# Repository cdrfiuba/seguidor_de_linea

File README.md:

# Robot Seguidor de Línea

Test de seguidor de línea para competiciones.
Nombre pendiente.

## Estructura del proyecto
Boceto de la estructura del proyecto

```bash
.
├── placa_sensor
│   ├── kicad_sch
│   └── kicad_pcb
├── placa_seguidor
│   ├── kicad_sch
│   └── kicad_pcb
├── modelo
│   └── seguidor.FCStd
├── include
│   ├── file1.h
│   └── file2.h
├── src
│   ├── file1.ino
│   └── file2.ino
├── res
│   ├── datasheets.pdf
│   ├── images.png
│   └── referencias o links
└── README.md
```

## Requisitos
 - 20cm largo x 14cm de ancho x 10cm de alto
 - Area mínima de 23mm x 14mm. Visible. No pueden ser secciones de la batería.
 - No control remoto, o que solo de la orden de salida
 - Indicador luminoso (fijo o intermitente) que muestra cuando el robot inicia a correr.
 - Ruedas sin adherentes

## TODOs
 - ~~Rediseñar la placa de sensores (corregir errores) y mandar al lci~~
 - ~~Puente H~~
 - ~~Arduino Nano o ATmega328~~ y programarlo
 - ~~Comprar Placa Experimental~~
 - ~~Elegir batería ~~
 - Hacer un diagrama tal vez de como seguir el proyecto
 - ~~Hacér una bitácora~~ (subirla al repo?)
 - Agregar pagina de documentación (KiBot)
 - ~~Agregar una lista de compras que puedan editar todos~~
 - ~~Terminar de Soldar/limpiar modulo de sensores chequeando continuidad (Ciin lo hace el jueves)~~
 - ~~Probar modulo se sensores con arduino (Armar código de prueba) ~~
 - Comprar Resistencias, capacitores (1206), diodos schottsky, hembra y macho (90 grados)
 - Soldar puente h anterior para probar
 - Medir las ruedas/bandas de caucho que se usará en la compe
 - Ajustar el modelo 3D del interior de la rueda
 - Soldar placa

## Artículos pendientes
 - 4 Capacitores 100nf (Puente H)
 - 8 x Diodos Schottsky 1N4007  (Puente H)
 - 1R de 1K y 1 de 330 SMD (1206)
 - 1 (+1) 74HC14 Schmitt Trigger THT
 - 2 DIP14

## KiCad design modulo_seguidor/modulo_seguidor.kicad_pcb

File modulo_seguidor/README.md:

# Modulo Seguidor

Este módulo ejecuta las funciones propias de un seguidor de línea, procesar las lecturas del módulo sensor, e integra el puente H L298N para dirigir los motores.

Vista previa de la placa desde arriba

## Diagrama

## TODOs
 - ~~Revisar las medidas de la placa (tomar en cuenta los bordes de la placa que no tienen agujeros)~~
 - Revisar los footprints de las resistencias y de los capacitores
 - Hacer espacio para la ruedita omnidireccional
 - ~~Acomodar los componentes y hacer las conexiones~~
 - Exportar a un modelo 3D (opcional)
 - ~~Probar en placa separada el modulo puente H~~
 - ~~Reemplazar conexiones de cables por housings~~

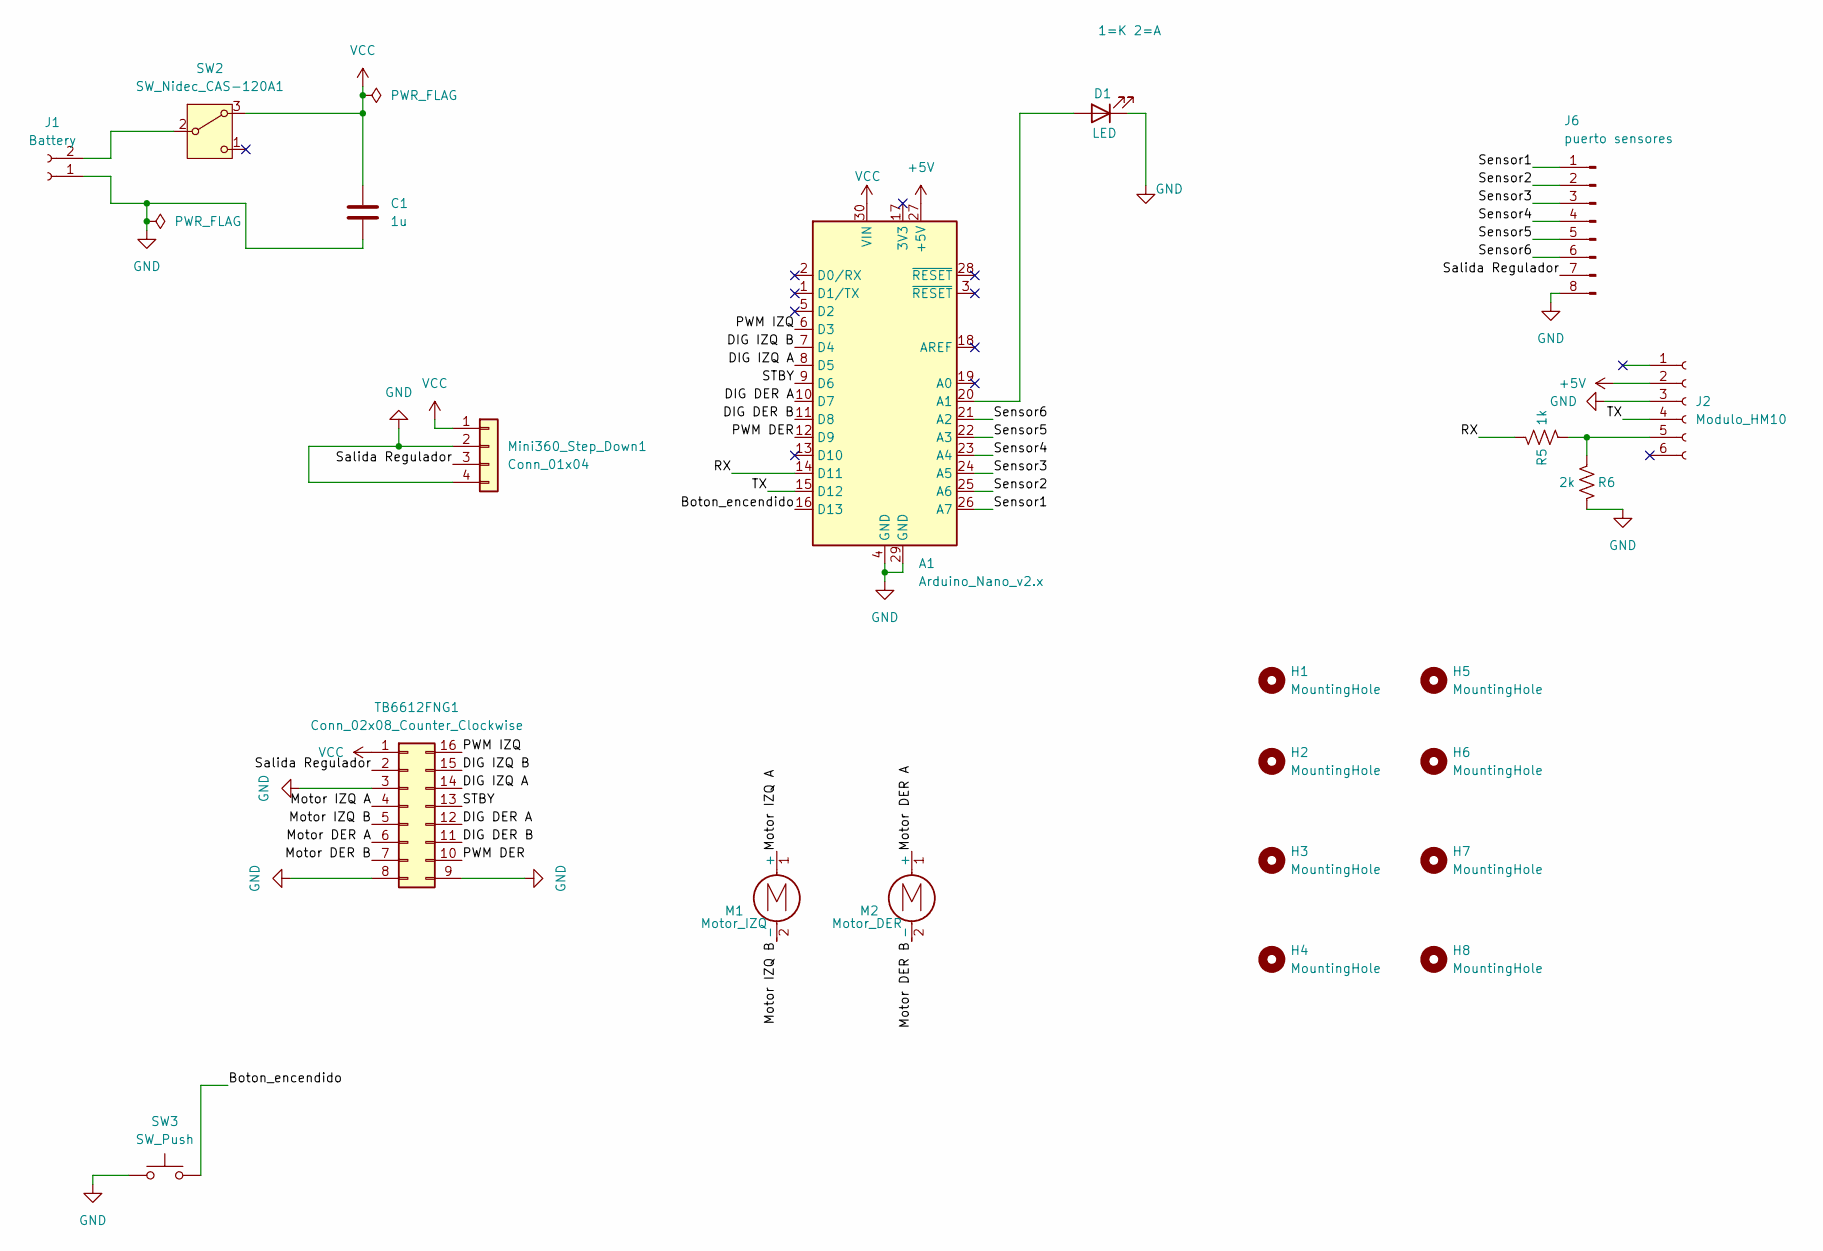
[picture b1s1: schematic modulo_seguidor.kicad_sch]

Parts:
A1: Arduino_Nano_v2.x; Arduino_Nano
C1: 1u; C_Disc_D5.0mm_W2.5mm_P5.00mm
D1: LED; LED_D5.0mm
H1, H2, H3, H4, H5, H6, H7, H8: MountingHole; MountingHole_3.2mm_M3
J1: Battery; Molex_KK-254_AE-6410-02A_1x02_P2.54mm_Vertical
J2: Modulo_HM10; PinSocket_1x06_P2.54mm_Horizontal
J6: puerto sensores; PinSocket_1x08_P2.54mm_Horizontal
M1: Motor_IZQ; Molex_KK-254_AE-6410-02A_1x02_P2.54mm_Vertical
M2: Motor_DER; Molex_KK-254_AE-6410-02A_1x02_P2.54mm_Vertical
Mini360_Step_Down1: Conn_01x04; Mini360_step-down
R5: 1k; R_Axial_DIN0207_L6.3mm_D2.5mm_P10.16mm_Horizontal
R6: 2k; R_Axial_DIN0207_L6.3mm_D2.5mm_P10.16mm_Horizontal
SW2: SW_Nidec_CAS-120A1; SolderWire-0.5sqmm_1x03_P4.6mm_D0.9mm_OD2.1mm
SW3: SW_Push; SW_PUSH_6mm_H5mm
TB6612FNG1: Conn_02x08_Counter_Clockwise; MODULE_ROB-14450

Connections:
+5V: A1.27 (+5V), J2.2
/Boton_encendido: A1.16 (D13), SW3.2
/DIG DER A: A1.10 (D7), TB6612FNG1.12
/DIG DER B: A1.11 (D8), TB6612FNG1.11
/DIG IZQ A: A1.8 (D5), TB6612FNG1.14
/DIG IZQ B: A1.7 (D4), TB6612FNG1.15
/Motor DER A: M2.1 (+), TB6612FNG1.6
/Motor DER B: M2.2 (-), TB6612FNG1.7
/Motor IZQ A: M1.1 (+), TB6612FNG1.4
/Motor IZQ B: M1.2 (-), TB6612FNG1.5
/PWM DER: A1.12 (D9), TB6612FNG1.10
/PWM IZQ: A1.6 (D3), TB6612FNG1.16
/RX: A1.14 (D11), R5.2
/STBY: A1.9 (D6), TB6612FNG1.13
/Salida Regulador: J6.7, Mini360_Step_Down1.3, TB6612FNG1.2
/Sensor1: A1.26 (A7), J6.1
/Sensor2: A1.25 (A6), J6.2
/Sensor3: A1.24 (A5), J6.3
/Sensor4: A1.23 (A4), J6.4
/Sensor5: A1.22 (A3), J6.5
/Sensor6: A1.21 (A2), J6.6
/TX: A1.15 (D12), J2.4
GND: A1.4 (GND), A1.29 (GND), C1.2, D1.1 (K), J1.1, J2.3, J6.8, Mini360_Step_Down1.2, Mini360_Step_Down1.4, R6.2, SW3.1, TB6612FNG1.3, TB6612FNG1.8, TB6612FNG1.9
unnamed: A1.20 (A1), D1.2 (A)
unnamed: J1.2, SW2.2 (B)
unnamed: J2.5, R5.1, R6.1
VCC: A1.30 (VIN), C1.1, Mini360_Step_Down1.1, SW2.3 (A), TB6612FNG1.1

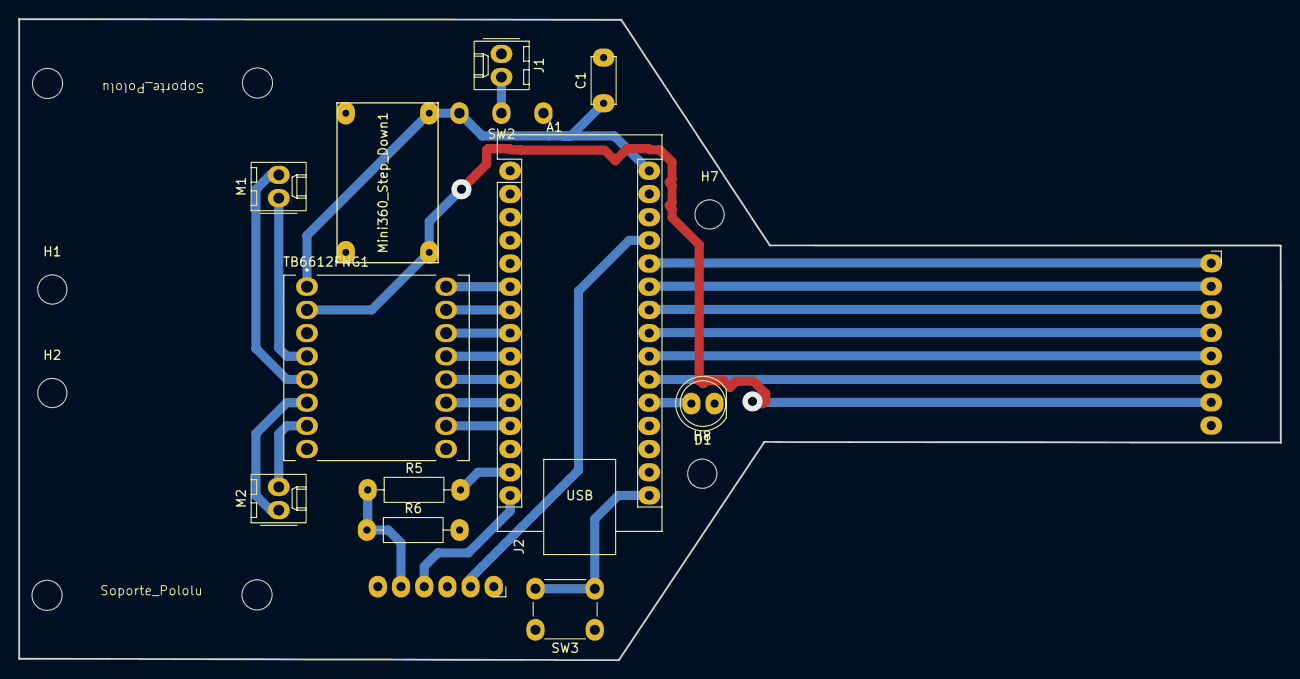
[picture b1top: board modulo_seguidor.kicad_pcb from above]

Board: 2 copper layers, 138.2 x 70.2 mm, 24 parts (0 on the bottom side), 27 nets.

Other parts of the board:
Soporte_Pololu: Soporte_Pololu
Soporte_Pololu#2: Soporte_Pololu

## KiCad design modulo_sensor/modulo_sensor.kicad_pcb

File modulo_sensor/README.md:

# Modulo de sensores

Este módulo se encarga de la lectura de la línea.

[comment]: Hacer_alguna_descripción_más

Vista previa de la PCB desde arriba

Vista previa de la PCB desde abajo

## TODOs
En orden de prioridad
- ~~Automatizar exportar los archivos de fabricación~~
- Hacer las pistas más grandes si es posible
- El script debe exportar a PDF ambos lados en la misma hoja conservando las dimensiones para imprimir el circuito.
- Exportar a otros formatos (SVG, STEP, etc)
- Agregar alguna compatibilidad para Windows(?
- Agregar algun check para el momento de subir a Github
- Tal vez agregar algunas opciones para controlar el script(?
- Cambiar las rutas relativas con alguna variable de entorno(?

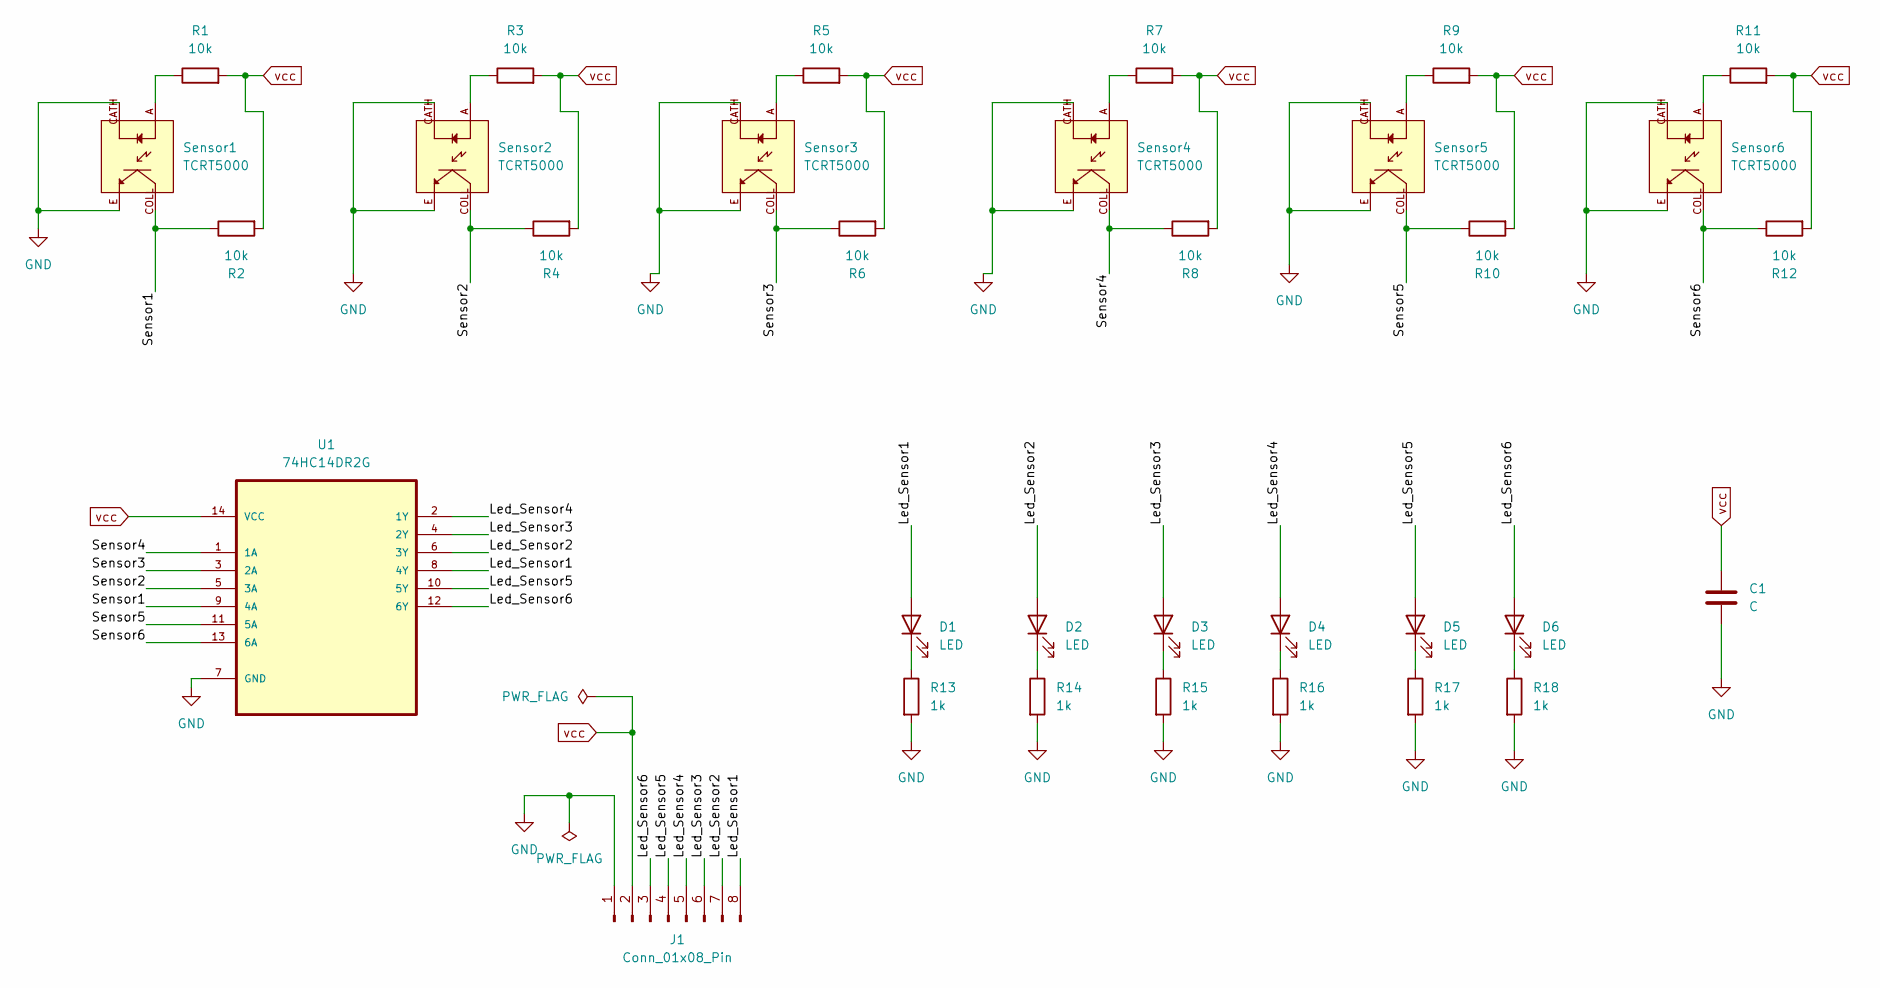
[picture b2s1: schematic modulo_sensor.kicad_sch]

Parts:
C1: C; C_Disc_D3.0mm_W1.6mm_P2.50mm
D1, D2, D3, D4, D5, D6: LED; LED_1206_3216Metric_Pad1.42x1.75mm_HandSolder
J1: Conn_01x08_Pin; PinHeader_1x08_P2.54mm_Horizontal
R1, R2, R3, R4, R5, R6, R7, R8, R9, R10, R11, R12: 10k; R_0805_2012Metric_Pad1.20x1.40mm_HandSolder
R13, R14, R15, R16, R17, R18: 1k; R_0805_2012Metric_Pad1.20x1.40mm_HandSolder
Sensor1, Sensor2, Sensor3, Sensor4, Sensor5, Sensor6: TCRT5000; OPTO_TCRT5000_ancho; PARTREV 1.7
U1: 74HC14DR2G; DIP-14_W7.62mm_Socket; MPN 74HC14DR2G

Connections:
/Led_Sensor1: D1.2 (A), J1.8, U1.8 (4Y)
/Led_Sensor2: D2.2 (A), J1.7, U1.6 (3Y)
/Led_Sensor3: D3.2 (A), J1.6, U1.4 (2Y)
/Led_Sensor4: D4.2 (A), J1.5, U1.2 (1Y)
/Led_Sensor5: D5.2 (A), J1.4, U1.10 (5Y)
/Led_Sensor6: D6.2 (A), J1.3, U1.12 (6Y)
/Sensor1: R2.1, Sensor1.COLL, U1.9 (4A)
/Sensor2: R4.1, Sensor2.COLL, U1.5 (3A)
/Sensor3: R6.1, Sensor3.COLL, U1.3 (2A)
/Sensor4: R8.1, Sensor4.COLL, U1.1 (1A)
/Sensor5: R10.1, Sensor5.COLL, U1.11 (5A)
/Sensor6: R12.1, Sensor6.COLL, U1.13 (6A)
GND: C1.2, J1.1, R13.2, R14.2, R15.2, R16.2, R17.2, R18.2, Sensor1.CATH, Sensor1.E, Sensor2.CATH, Sensor2.E, Sensor3.CATH, Sensor3.E, Sensor4.CATH, Sensor4.E, Sensor5.CATH, Sensor5.E, Sensor6.CATH, Sensor6.E, U1.7 (GND)
unnamed: D1.1 (K), R13.1
unnamed: D2.1 (K), R14.1
unnamed: D3.1 (K), R15.1
unnamed: D4.1 (K), R16.1
unnamed: D5.1 (K), R17.1
unnamed: D6.1 (K), R18.1
unnamed: R1.1, Sensor1.A
unnamed: R3.1, Sensor2.A
unnamed: R5.1, Sensor3.A
unnamed: R7.1, Sensor4.A
unnamed: R9.1, Sensor5.A
unnamed: R11.1, Sensor6.A
vcc: C1.1, J1.2, R1.2, R2.2, R3.2, R4.2, R5.2, R6.2, R7.2, R8.2, R9.2, R10.2, R11.2, R12.2, U1.14 (VCC)

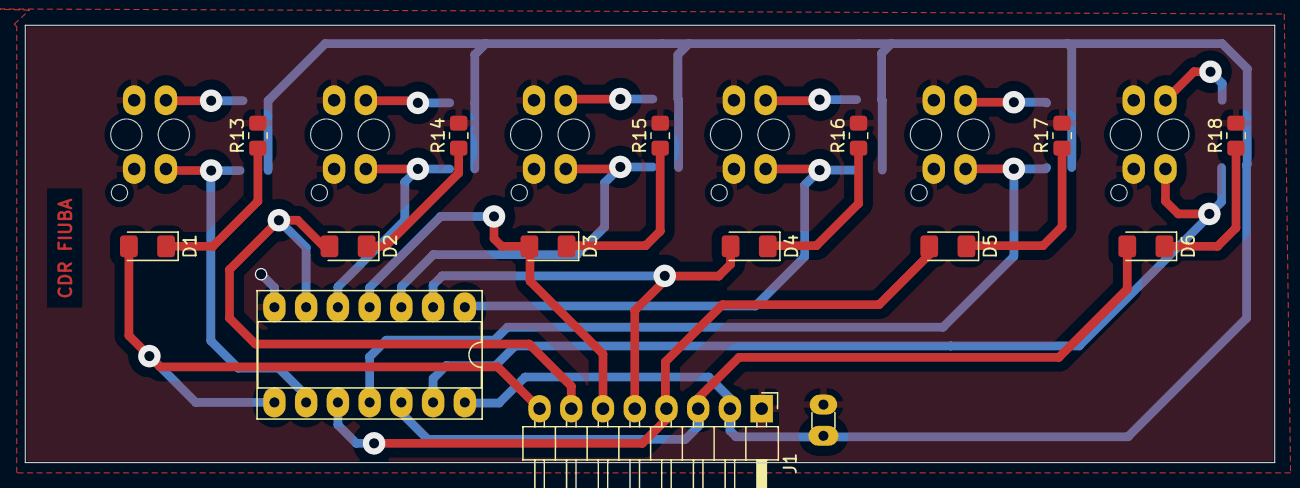
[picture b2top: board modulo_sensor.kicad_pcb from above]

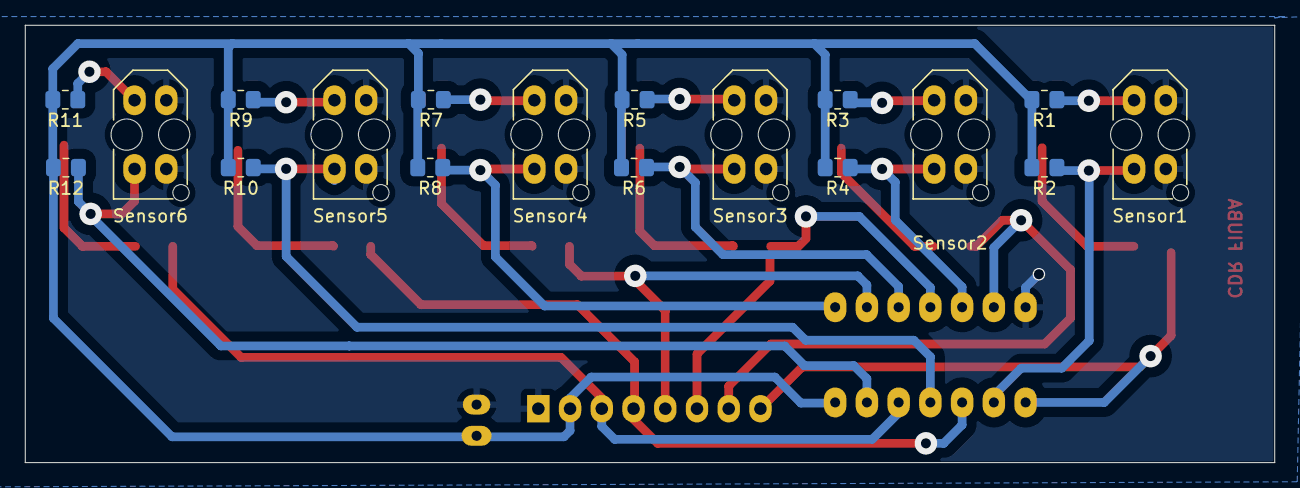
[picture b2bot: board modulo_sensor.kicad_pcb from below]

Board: 2 copper layers, 100.0 x 35.0 mm, 33 parts (18 on the bottom side), 26 nets.

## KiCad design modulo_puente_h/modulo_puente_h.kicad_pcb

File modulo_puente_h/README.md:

# Modulo Puente H

Este módulo se encarga de controlar los motores a partir de las entradas recibidas por sus pines.

Las pistas azules representan conexiones físicas cableadas por nosotros ya que el diseño no es posible en una placa simple faz.

## TODOs
 - [ ] Revisar las medidas de la placa
 - [ ] Hacer los agujeros para las medidas del modelo 3D
 - [ ] El regulador de tensión debería ir en este módulo?
 - [ ] Revisar las conexiones
 - [ ] Replantearse el diseño del puente h, ¿Qué tensión tienen los motores?

#### Nota

Considerar que se podría diseñar todo en la parte posterior y soldar los componentes del lado que no tiene cobre.

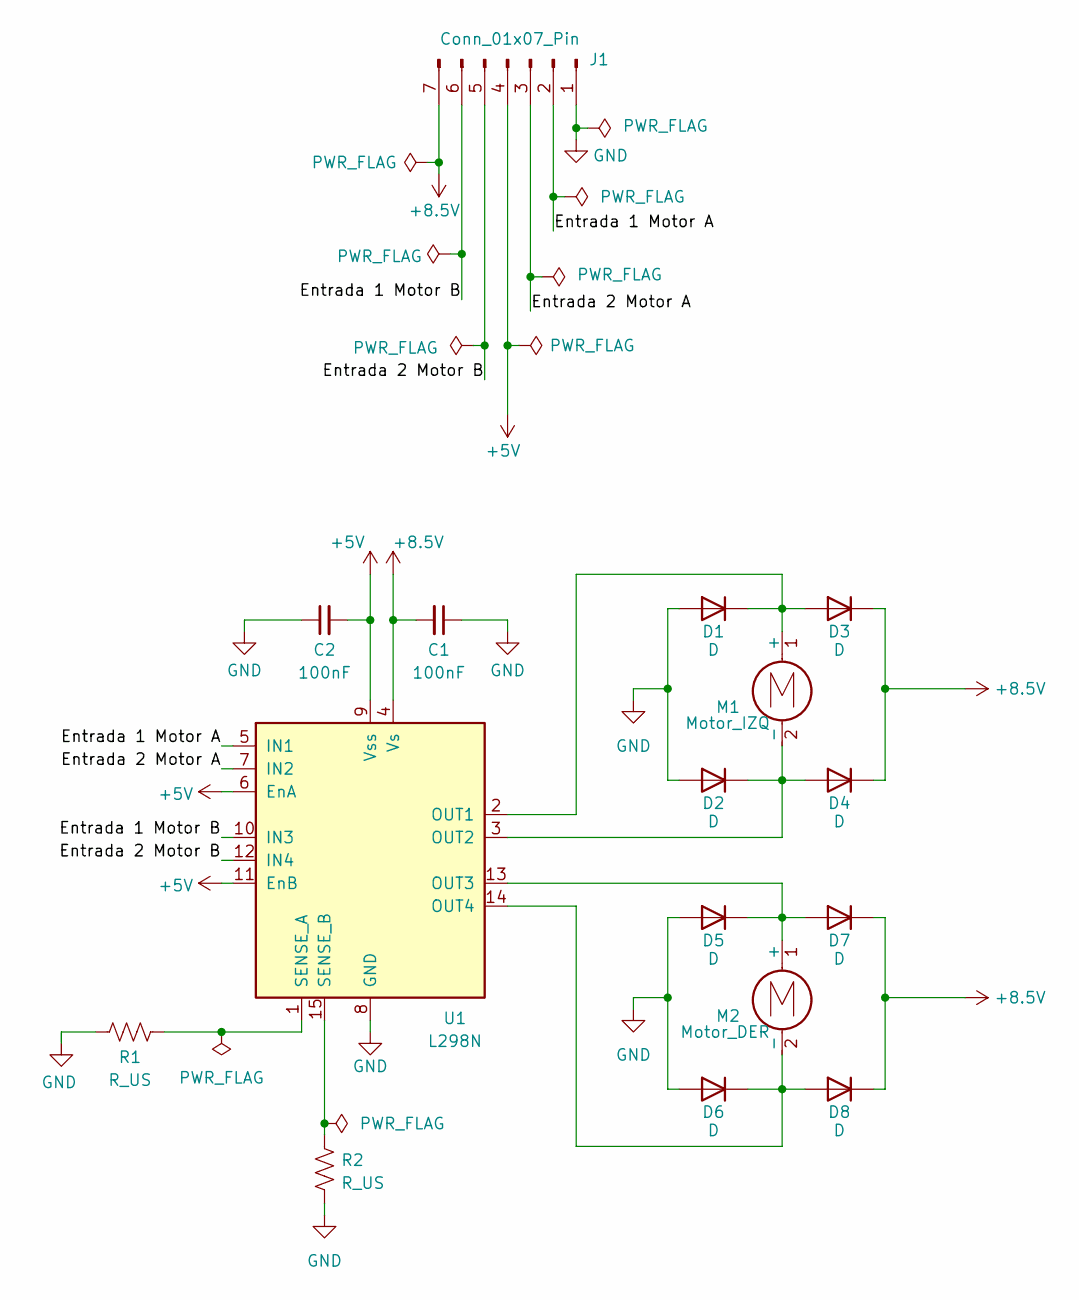
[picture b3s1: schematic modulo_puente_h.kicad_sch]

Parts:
C1, C2: 100nF; C_Disc_D7.0mm_W2.5mm_P5.00mm
D1, D2, D3, D4, D5, D6, D7, D8: D; D_DO-41_SOD81_P7.62mm_Horizontal
J1: Conn_01x07_Pin; PinHeader_1x07_P2.54mm_Vertical
M1: Motor_IZQ; R_Axial_DIN0207_L6.3mm_D2.5mm_P2.54mm_Vertical
M2: Motor_DER; R_Axial_DIN0207_L6.3mm_D2.5mm_P2.54mm_Vertical
R1, R2: R_US; R_0805_2012Metric_Pad1.20x1.40mm_HandSolder
U1: L298N; TO-220-15_P2.54x5.08mm_StaggerOdd_Lead4.58mm_Vertical

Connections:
+5V: C2.2, J1.4, U1.6 (EnA), U1.9 (Vss), U1.11 (EnB)
+8.5V: C1.2, D3.1 (K), D4.1 (K), D7.1 (K), D8.1 (K), J1.7, U1.4 (Vs)
/Entrada 1 Motor A: J1.2, U1.5 (IN1)
/Entrada 1 Motor B: J1.6, U1.10 (IN3)
/Entrada 2 Motor A: J1.3, U1.7 (IN2)
/Entrada 2 Motor B: J1.5, U1.12 (IN4)
GND: C1.1, C2.1, D1.2 (A), D2.2 (A), D5.2 (A), D6.2 (A), J1.1, R1.2, R2.1, U1.8 (GND)
unnamed: D1.1 (K), D3.2 (A), M1.1 (+), U1.2 (OUT1)
unnamed: D2.1 (K), D4.2 (A), M1.2 (-), U1.3 (OUT2)
unnamed: D5.1 (K), D7.2 (A), M2.1 (+), U1.13 (OUT3)
unnamed: D6.1 (K), D8.2 (A), M2.2 (-), U1.14 (OUT4)
unnamed: R1.1, U1.1 (SENSE_A)
unnamed: R2.2, U1.15 (SENSE_B)

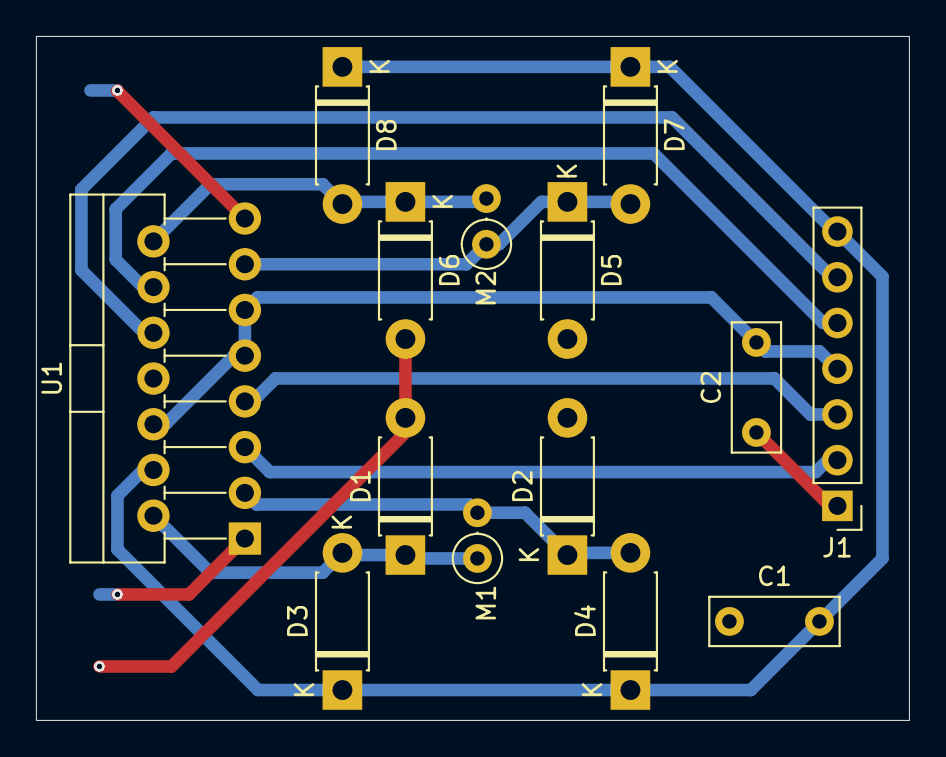
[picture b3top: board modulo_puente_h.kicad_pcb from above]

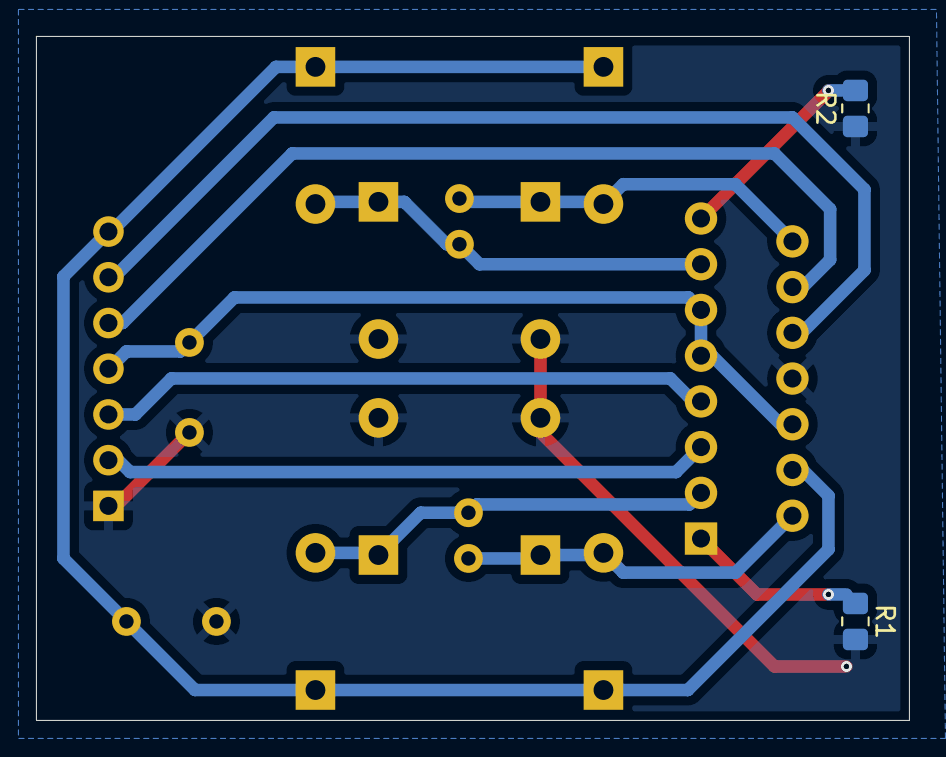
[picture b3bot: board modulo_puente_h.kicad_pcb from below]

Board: 2 copper layers, 48.5 x 38.0 mm, 16 parts (2 on the bottom side), 13 nets.

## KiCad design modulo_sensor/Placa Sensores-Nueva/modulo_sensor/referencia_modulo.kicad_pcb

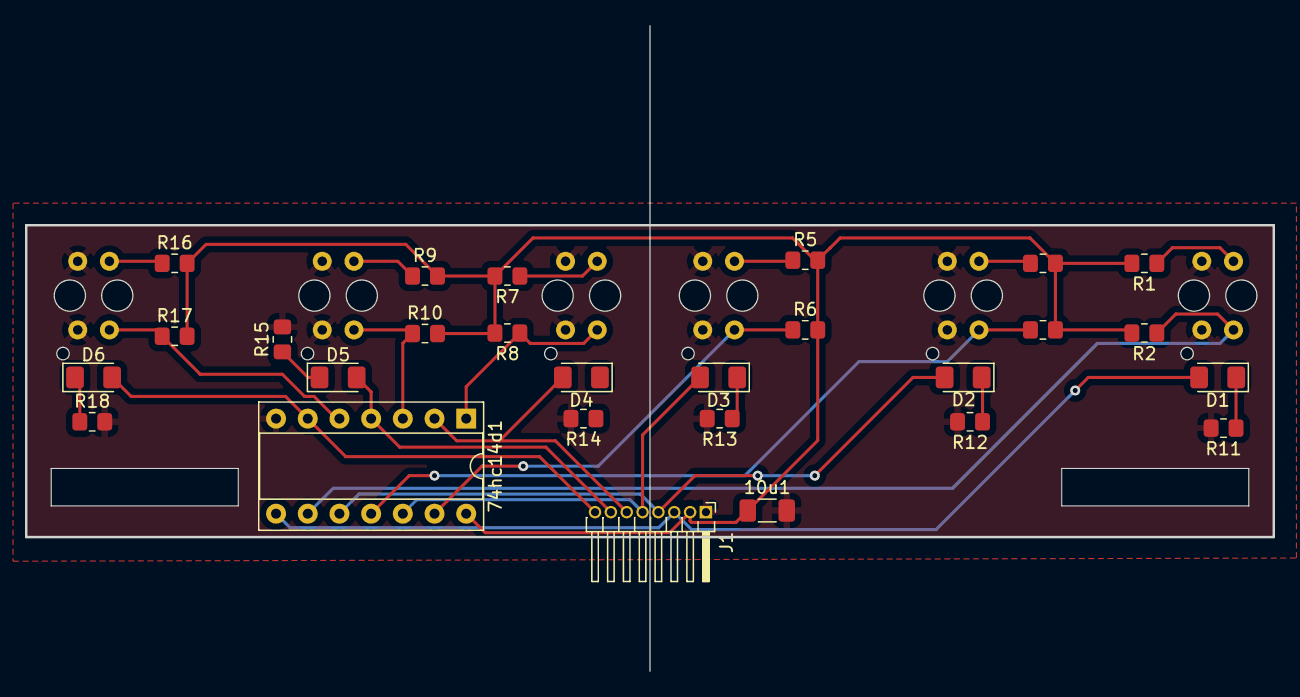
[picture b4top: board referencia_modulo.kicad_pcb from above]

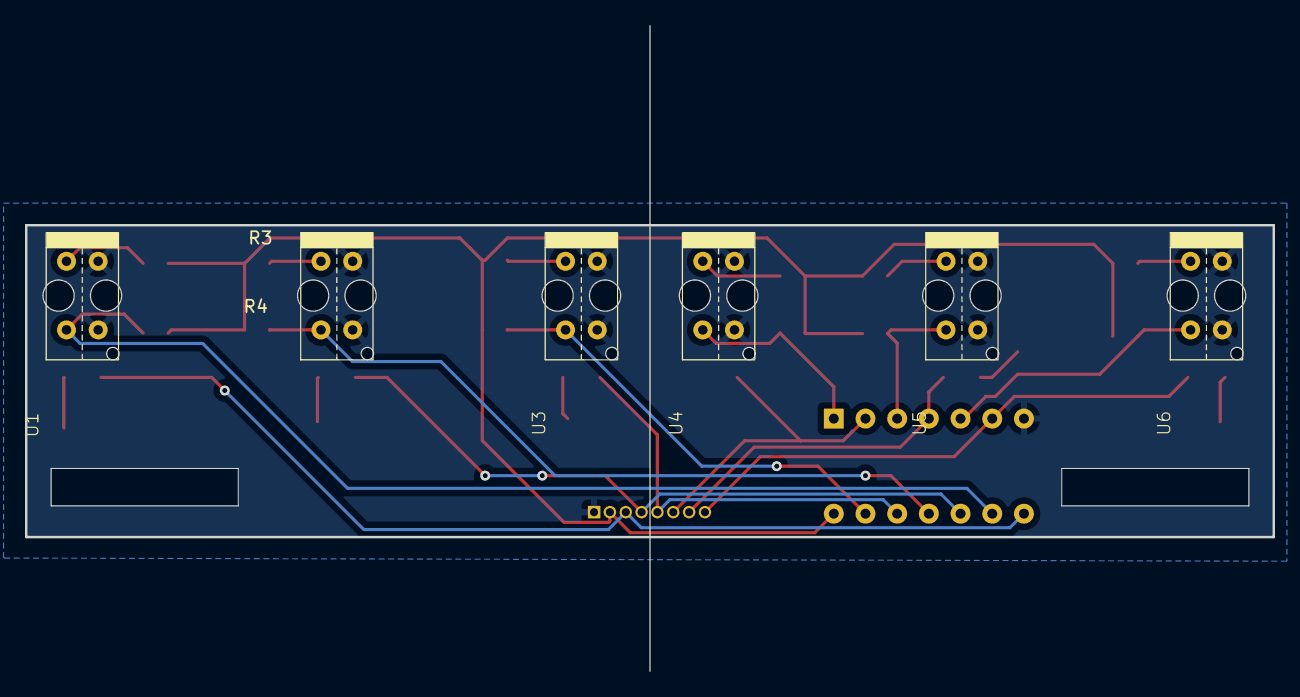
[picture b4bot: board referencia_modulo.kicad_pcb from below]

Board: 2 copper layers, 100.0 x 51.7 mm, 33 parts (6 on the bottom side), 26 nets.

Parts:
10u1: CAP; C_1206_3216Metric_Pad1.33x1.80mm_HandSolder
74hc14d1: A_14-LC-TT; DIP-14_W7.62mm_Socket
D1, D2, D3, D4, D5, D6: LED; LED_1206_3216Metric_Pad1.42x1.75mm_HandSolder
J1: Conn_01x08_Pin; PinHeader_1x08_P1.27mm_Horizontal
R1, R3, R5, R7, R9, R16: 220; R_0805_2012Metric_Pad1.20x1.40mm_HandSolder
R2, R4, R6, R8, R10, R17: 10k; R_0805_2012Metric_Pad1.20x1.40mm_HandSolder
R11, R12, R13, R14, R15, R18: 1k; R_0805_2012Metric_Pad1.20x1.40mm_HandSolder
U1, U2, U3, U4, U5, U6: TCMT4106; tcrt5000

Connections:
/sensor1: 74hc14d1.8, D1.2 (A), J1.3
/sensor1_unfiltered: 74hc14d1.9, R2.1, U1.16
/sensor2: 74hc14d1.10, D2.2 (A), J1.4
/sensor2_unfiltered: 74hc14d1.11, R4.1, U2.16
/sensor3: 74hc14d1.12, D3.2 (A), J1.5
/sensor3_unfiltered: 74hc14d1.13, R6.1, U3.16
/sensor4: 74hc14d1.2, D4.2 (A), J1.6
/sensor4_unfiltered: 74hc14d1.1, R8.1, U4.16
/sensor5: 74hc14d1.4, D5.2 (A), J1.7
/sensor5_unfiltered: 74hc14d1.3, R10.1, U5.16
/sensor6: 74hc14d1.6, D6.2 (A), J1.8
/sensor6_unfiltered: 74hc14d1.5, R17.1, U6.16
GND: 10u1.2, 74hc14d1.7, J1.1, R11.2, R12.2, R13.2, R14.2, R15.2, R18.2, U1.2, U1.15, U2.2, U2.15, U3.2, U3.15, U4.2, U4.15, U5.2, U5.15, U6.2, U6.15
unnamed: D1.1 (K), R11.1
unnamed: D2.1 (K), R12.1
unnamed: D3.1 (K), R13.1
unnamed: D4.1 (K), R14.1
unnamed: D5.1 (K), R15.1
unnamed: D6.1 (K), R18.1
unnamed: R1.1, U1.1
unnamed: R3.1, U2.1
unnamed: R5.1, U3.1
unnamed: R7.1, U4.1
unnamed: R9.1, U5.1
unnamed: R16.1, U6.1
VCC: 10u1.1, 74hc14d1.14, J1.2, R1.2, R2.2, R3.2, R4.2, R5.2, R6.2, R7.2, R8.2, R9.2, R10.2, R16.2, R17.2

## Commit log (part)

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2024-09-18 docs: Boceto de la estructura del proyecto
2024-09-18 docs: Agregados requisitos para el robot
2024-09-18 docs: agrego referencias a otros proyectos similares
2024-09-18 docs: Agrego imágenes de referencia
2024-09-18 docs: agregar todos para organizar el avance
2024-09-22 docs: Agrego TODOs discutidos en la semana 3
2024-09-28 doc: Agrego datasheets de los sensores infrarrojos y del schmitt-trigger
2024-09-28 feat: Agrego proyecto de kicad del modulo de sensores
2024-09-28 feat: Agrego librerias del sensor TCRT5000
    Liberías de símbolos, huellas y ste|p (modelo 3D)
2024-09-28 feat: Agrego libería del 74HC14DR2G
    Librería de símbolos, footprints y step
2024-09-28 chore: Update de las configuraciones del modulo sensor
2024-09-28 feat: Agrego esquemático del sensor
2024-09-28 fix: Actualizo los valores de las resistencias y el footprint del led
2024-09-28 feat: pcb del modulo de sensores con el 74HC en vertical
2024-09-28 feat: Agrego referencia de la placa de sensores del SDL anterior
2024-09-28 refactor: Intercambio los labels de los pines y del 74HC para acomodarlos en la pcb
2024-09-28 feat: diseño casi funcional de la pcb del modulo sensores.
    Todas las conexiones están hechas pero hay warnings y errores del DRC.
2024-09-28 refactor: Cambio los footprints de todas las resistencias THT por SMD
2024-09-28 refactor: Reduzco la distancia entre los sensores centrales dentro de 20mm
    Ahora hay 18,07mm de centro a centro en los sensores 3 y 4
2024-09-28 fix: Arreglo algunas conexiones sueltas y relleno B.Cu con GND
2024-09-28 refactor: Elimino boceto con el 74HC horizontal
2024-09-29 docs: Agrego preview de la pcb.
    En el README se dejaran notas y una preview del último estado de la pcb
2024-09-29 feat: Script para automatizar exportar el svg desde cli en linux
    Dar permiso con chmod +x ./export.sh
2024-09-29 docs: Agrego proporción a la preview
2024-10-01 refactor: Pongo el integrado en horizontal
    Está todo conectado como antes
2024-10-01 refactor: Los sensores ahora están en la capa de abajo
2024-10-01 refactor: Cambio las huellas de los led por SMDs
2024-10-01 fix: Actualizo la preview
2024-10-01 fix: Cambio las huellas de los leds por smd en el esquemático
2024-10-02 feat: Agrego los modelos 3D para el visor 3D de KiCad
2024-10-02 refactor: Reacomodos menores y reduzco el tamaño de la placa
2024-10-02 feat: Actualizo el script para exportar preview de B y F
2024-10-02 refactor: Reodeno los pines para acomodarlos en la pcb
2024-10-02 refactor: Reorganizo la pcb y la hago más chica
2024-10-02 chore: Pequeño cambio de configuracion del kicad_pro
2024-10-02 refactor: Reduzo la placa para redondear la medida
2024-10-02 fix: No había guardado en el anterior commit
2024-10-03 refactor: Cambio de margen de rutas a 0,3mm y arreglo algunos checks
    Las infracciones son por la cercania de los pines del conector J1
2024-10-05 refactor: Actualizo el ancho de las pistas a 0,6
2024-10-05 fix: Agrego valor a la huella del capacitor
2024-10-05 refactor: Actualizo los archivos de fabricación
2024-10-05 feat: Archivo .zip con los archivos de fabricación actualizados
2024-10-05 fix: Agrego exclusiones a las infracciones de margen de los pines de J1
2024-10-05 feat: Actualizo el README con TODOs y muevo las previews
2024-10-05 docs: Agrego TODO
2024-10-05 docs: Tacho un TODO
2024-10-05 refactor: Alejo pistas de los bordes (por las dudas)
2024-10-06 docs: Agrego imagen con el pinout del arduino Nano
2024-10-06 feat: Agrego esquemático de la placa del seguidor
2024-10-06 feat: Aplico configuraciones para simular una perfboard para el diseño
2024-10-06 docs: Documento el modulo seguidor
2024-10-06 refactor: Actualizo huellas del esquemático
2024-10-06 feat: Agrego boceto de la placa del modulo seguidor y su preview
2024-10-06 style: Agrego las medidas de los lados en la pcb del modulo seguidor
2024-10-06 fix: Arreglo la preview del modulo seguidor con el nuevo archivo
2024-10-06 fix: Arreglo previews rotas del modulo sensor
2024-10-06 fix: Actualizo archivos de fabricación a la última versión
2024-10-06 fix: Arreglo las previews del modulo sensor
2024-10-09 chore: Agrego aclaración para el led D6 espejado
2024-10-09 docs: Agrego TODOs al main
2024-10-09 feat: Actualizo las previews del modulo sensor a la ultima versión
2024-10-09 feat: Agrego argumentos al script para indicarle exportar la fabricacion
2024-10-09 feat: Agrego argumento help al script
2024-10-12 docs: Agrego documento de ayuda sobre el diseño de las pcbs
2024-10-12 feat: Agrego los cables en la pcb del modulo seguidor
2024-10-12 refactor: Reordeno la pcb del modulo seguidor y sus conexiones
2024-10-12 refactor: Hago las conexiones n poco más cortas y rectas
2024-10-13 refactor: Cambio las conexiones en los pines del modulo seguidor para compactar la pcb
2024-10-13 refactor(modulo_seguidor): Intercambio dos pines para hacer los cables más cortos
2024-10-13 feat(modulo_seguidor): Agrego partes no perforadas y lo referencio en la documentacion
2024-10-13 docs: Elimino TODOs de la lista
2024-10-13 refactor(modulo_sensor): Elimino archivos de fabricacion
    Los archivos estarán disponibles en las releases junto con los modelos y
    otros archivos finales del proyecto.
2024-10-13 faet(modulo_sensor): El script exporta un modelo 3D del pcb
2024-10-13 docs(modulo_sensores): completo un TODO
2024-10-19 refactor(modulo_sensor): Cambio la huella del pin por una de 2,5mm
2024-10-19 refactor(modulo_sensor): Acomodo algunas pistas de cobre
2024-11-02 docs: Updateo TODOs
2024-11-04 res: Agrego datasheet del puente H
2024-11-04 res: Agrego datasheet del regulador de tensión
2024-11-05 test(modulo_sensor): Agrego test para los sensores
2024-11-05 docs: Agrego lista de articulos pendientes
2024-11-05 Agrego tareas al TODOs
2024-11-05 Agrego en lista de compras
2024-11-16 feat(puente-h): Agrego esquemático del puente H
2024-11-16 fix(puente-h): Las salidas de sensor no tenian PWR_FLAG
2024-11-17 refactor(puente-h):Modifico el orden de los pines de conexión
2024-11-17 feat(puente-h): Agrego pcb del puente H
2024-11-17 docs(puente-h): Agrego documentacion y vista previa de la placa
2024-11-17 refactor(puente-h): Reordeno los pines
2024-11-17 refactor(puente-h): Achico la placa
2024-11-17 docs(puente-h): Actualizo la preview de la placa
2024-11-22 docs(puente-h): Link colgado de una imagen anterior
2024-12-06 fix: Las pistas van del lado de las soldaduras
    No se puede soldar en el plástico :/
2025-03-30 refactor!: Update de versión Kicad y corrijo nombres del esquemático
2025-03-30 fix: Agrego PWR_FLAGs para el ERC de Kicad y footprint del l298
2025-03-30 refactor: Reorganizo las etiquetas de los pines
2025-03-30 refactor(puente-h): Ensancho espacios entre pistas
2025-03-30 fix(puente-h): Relleno la zona GND de la PCB
2025-04-03 docs(puente-h): Agrego preview en pdf para imprimir
2025-05-10 feat: Added PCB export to PDF
2025-05-11 feat(seguidor): Corrijo errores de DRC esquemático
2025-05-11 feat(modulo-seguidor): Agrego placa con el seguidor y el puente h incluidos
2025-05-11 feat(modulo_seguidor): Agrego boceto PCB del seguidor + puente H
2025-05-11 refactor(modulo-seguidor): Reorganizo vías y limpio carpeta de puente h
2025-05-24 refactor(modulo-seguidor): Cambio resistencia del LED de THT por SMD
2025-05-24 refactor!(modulo-seguidor): Modifico forma de la placa
2025-05-24 refactor(modulo-seguidor): Cambio huella de motores a Housing
2025-05-24 refactor(modulo-seguidor): Continuo el boceto de la placa
2025-05-24 feat(Modulo_seguidor) "Diseño con todo conectado + detalles"
    Cambie de lugar algunos pines del arduino para mejor llega a las conexiones . Entre ellos :
    - Botón Encendido del D15 al D16
    - Encender Botón: de A7 a A1
    - Se deja un especio en el medio donde iría apoyada la batería
    - Las conexiones rojas indican que por arriba se pasará un cable
    Propuesta: Si bien llegué a conectar la salida del regulador a la placa de sensores. Capaz sería conveniente alimentar esa placa con los 5V del arduino
2025-05-24 Cambio de pines de motores
    El anterior los había cambiado para probar pero como mi idea ahora es usar housing para conectar con cable por arriba vuelvo a poner las entradas del motor en orden
    PWM A = D ocho
    DIG A = D9
    PWM B = D10
    DIG B = D11
2025-05-24 Codigo Donatello actualizado
    En base al código que nos pasaron de Donatello le agregué las entradas correspondientes de nuestro seguidor
2025-05-24 Agrego los códigos que había realizado manu
    Para tenerlo a mano
2025-05-24 refactor(modulo-seguidor): Cambio conexiones de entrada del l298 por housings
2025-05-24 chore(modulo-seguidor): Modificaciones de archivo proyecto
2025-05-24 refactor(modulo-seguidor): Redistribución y cambio de entrada del puente por housing
2025-05-24 docs(modulo-seguidor): Agrego TODOs
2025-05-24 docs: Agrego TODOs para la próxima visita al LABI
2025-05-24 refactor(src): Muevo archivos de lugar
2025-05-25 Nueva placa de sensores mejor centrada
    Cambie de lugar los pines y con ello las conexiones para la versión final del seguidor
    Lo puse en otra carpeta para no borrar la versión actual
    La placa ahora mide exactamente 100 x 35 mm
2025-05-26 Agrego pasante de GND para Schmitt Trigger
    El GND del integrado queda muy aislado de todo el gnd, se agrega un pasante para soldar y asegurar que todas las tierras esten conectadas
2025-05-26 agrego medidas de la placa
2025-05-28 cambio tamaño de ruedas
    Ya saque las medidas de las ruedas y lo plasmé en el programa
2025-07-03 detalles
2025-07-04 Tamaño de pads
2025-07-26 refactor!(Modulo seguidor): Cambio pines de sensores a analógicos, PWM, pin de botón, y led
2025-07-26 refactor(modulo-seguidor): Cambio pines de led y de boton del seguidor
2025-07-26 refactor!(modulo-seguidor): Actualizo la pcb con los cambios del esquemático
2025-07-26 refactor(modulo-seguidor): Acomodo componentes de la batería, y pin de 5v del sensor
2025-07-26 reactor(modulo-seguidor): Modifico las pistas de VCC
    Los diodos de ambos motores ahora no son simétricos
2025-07-26 refactor(modulo-seguidor): Elimino jumpers de entradas de un motor del puente H
2025-07-26 refactor(modulo-seguidor): Reordeno los componentes del pcb
2025-07-26 cambios pequeños
2025-07-26 refactor(modulo-seguidor): Actualizo medidas y agrego zonas de exclusion para facilitar soldadura
2025-07-27 feat(modulo-seguidor): Agrego pequeño script para exportar pdf
2025-07-29 refactor(modulo-sensor): Elimino los archivos de la versión anterior de la placa
2025-07-29 refactor(modulo-sensor): Agrego flag explícita para exportar a pdf
2025-07-29 style(modulo-sensor): Cambio las posiciones de las medidas para mejor vista
2025-07-30 refactor(models): Elimino los archivos de respaldo
2025-07-30 chore(models): Elimino carpeta duplicada
    Diseños 3D pasa a llamarse models y elimino el archivo viejo
2025-07-30 fix(modulo-sensor): Arreglo pista no conectada y saco el texto de la capa EdgeCuts
2025-08-12 refactor(modulo-seguidor): Elimino jumpers por cables soldados
2025-08-12 style(modulo-seguidor): Acomodo el interruptor de la batería más al centro
2025-08-12 chore: Actualizo script para exportar las capas del módulo seguidor en orden
2025-08-12 refactor(modulo-seguidor): Actualizo disposicion de los componentes y agrego preview
2025-10-30 refactor(src): junto los casos en un solo archivo
    decido cual compilar a partir de definir una macro
2025-10-30 feat: Agrego test para motores
2025-10-30 chore: Agrego archivo por las dudas
2025-10-30 docs(src): Agrego breve descripcion de la estructura de src
2025-10-31 feat: Agrego prueba para setear motores al maximo
2025-11-01 feat(src): Agrego setup de pins del boton y el led del seguidor
2025-11-01 refactor(src): Elimino el condicional de cada archivo
2025-11-01 refactor(src): Agrego funcion para configurar todos los pines del seguidor
2025-11-01 feat(src): Porteo las versiones para utilizar los pines definidos en pins.h
2025-11-02 feat(src): Agrego funcion para leer pines de sensores digitales y analogicos con sobrecarga de funciones
2025-11-02 refactor(src): Actualizo la v3 para arrancar con un boton y manejo el led
2025-11-02 docs(src): Agrego TODOs
